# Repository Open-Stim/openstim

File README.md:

# <P align="center"> OPEN-STIM - OPEN SOURCE HARDWARE ARDUINO BASED ELECTRICAL STIMULATOR 
<table align='center'>
<tr align='center'>
<td align='center'>

Licence | OSHWA |
:-------------------------:|:-------------------------:|
 |  

</table> 
 
## <P align="center"> FEDERAL UNIVERSITY OF SÃO JOÃO DEL-REI – UFSJ
### <P align="center"> NEUROENGINEERING AND NEUROSCIENCE INTERDISCIPLINARY LABORATORY – LINNCE
&emsp; &emsp; &emsp; &emsp; &emsp; &emsp; &emsp; &emsp; &emsp; &emsp; &emsp; &emsp; &emsp; &emsp; &emsp; &emsp; &emsp; 

### DEVELOPED BY:
Maikon Lorran Santos - maikon.lorran@hotmail.com <br/>
João Daniel Nolasco - joaodani@hotmail.com <br/>
Vinícius Rosa Cota: - vrcota@ufsj.edu.br <br/>

### PROJECT'S GOAL
<P align="justify"> The main objective of the project was to develop and build a low-cost electrical stimulator for experimental stimulation electrophysiology
based on the Arduino platform, maximizing ease of use, versatility, and openness. The idea was to develop an output stage shield capable of 
delivering mono or biphasic pulses with constant current (even in face of varying output impedances) easily attachable to an Arduino microcontroller
board. Stimulation parameters (pulse frequency, pulse duration, number and polarity of phases) can be controlled by a touch screen and/or by knobs.
In this entry, we published the version which is controlled mostly by a touch screen display, but this can be easily substituted by manual controls 
(switches and additional knobs) with or without a LCD display to further reduce costs (variation not yet published). These variations and openness of 
the design (which is provisionally certified by OSHWA with UID BR000007) makes Open Stim a very flexible stimulation platform for experienced users and, 
at the same time, also a ready-to-use device for researchers not skilled on electronics. 

### DISCLAIMER
<P align="justify"> We offer this design as is and although it has been successfully tested with care and to the best of our knowledge, we do not provide any 
 warranty in any aspect.

### STIMULATOR PARAMETERS
-Current: 15 µA up to 1200 µA <br/>
-Frequency: 0.1 Hz up to 300 Hz <br/>
-Duty Cycle: 4 µs up to 1 s <br/>
-Biphasic Pulses <br/>
-Low battery indicator <br/>

### OPEN STIM

&emsp; &emsp; &emsp; 
### • More about the lab, at our website: [LINNce](https://ufsj.edu.br/vrcota/linnce.php)

### LICENSE
##### Documentation licensed under the Creative Commons Attribution Share Alike 4.0 International License

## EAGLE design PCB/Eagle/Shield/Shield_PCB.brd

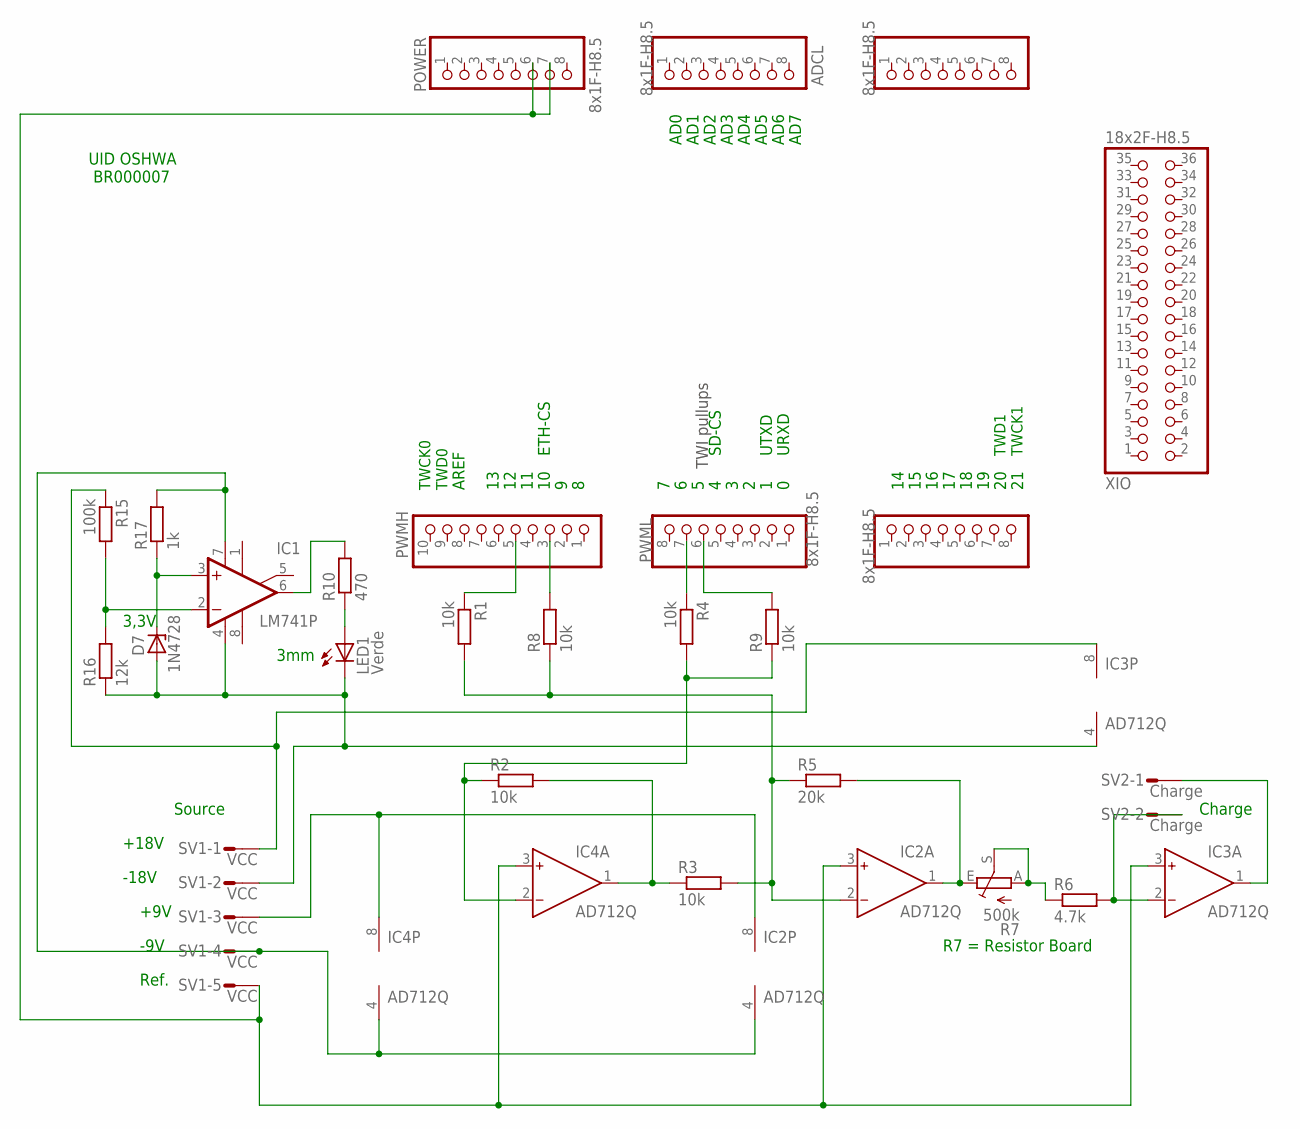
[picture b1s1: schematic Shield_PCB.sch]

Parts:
ADCH: 8x1F-H8.5; 1X08
ADCL: 8x1F-H8.5; 1X08
COMMUNICATION: 8x1F-H8.5; 1X08
D7: 1N4728; DO41Z10
IC1: LM741P; DIL08
IC2, IC3, IC4: AD712Q; DIL08
LED1: Verde; LED3MM
POWER: 8x1F-H8.5; 1X08
PWMH: 10x1F-H8.5; 1X10
PWML: 8x1F-H8.5; 1X08
R1, R2, R3, R4, R8, R9: 10k; 0207/10
R5: 20k; 0207/10
R6: 4.7k; 0207/10
R7: 500k; B64Y
R10: 470; 0207/10
R15: 100k; 0207/10
R16: 12k; 0207/10
R17: 1k; 0207/10
SV1: VCC; L05P
SV2: Charge; L02P
XIO: 18x2F-H8.5; 2X18

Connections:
unnamed: IC4.2 (IN-), R2.1, R4.2, R9.1
unnamed: IC4.1 (OUT), R2.2, R3.1
unnamed: IC2.2 (IN-), R1.2, R3.2, R5.1, R8.1
unnamed: IC2.1 (OUT), R5.2, R7.E
unnamed: IC3.2 (IN-), R6.2, SV2.2
unnamed: R6.1, R7.A, R7.S
unnamed: IC3.1 (OUT), SV2.1
unnamed: PWMH.3, R8.2
unnamed: PWMH.5, R1.1
unnamed: PWML.7, R4.1
unnamed: PWML.6, R9.2
unnamed: IC3.8 (V+), R15.1, SV1.1
unnamed: D7.A, IC1.4 (V-), IC3.4 (V-), LED1.K (C), R16.1, SV1.2
unnamed: IC1.7 (V+), IC2.4 (V-), IC4.4 (V-), R17.2, SV1.4
unnamed: IC2.3 (IN+), IC3.3 (IN+), IC4.3 (IN+), POWER.6, POWER.7, SV1.5
unnamed: D7.C, IC1.3 (+IN), R17.1
unnamed: IC1.2 (-IN), R15.2, R16.2
unnamed: IC1.6 (OUT), R10.2
unnamed: LED1.A, R10.1
unnamed: IC2.8 (V+), IC4.8 (V+), SV1.3

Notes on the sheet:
TWI pullups
TWCK1
TWD1
TWCK0
TWD0
AD1
AD2
AD3
AD4
AD5
AD6
AD0
AREF
AD7
SD-CS
UTXD
URXD
ETH-CS
Source
Charge
R7 = Resistor Board
3,3V
3mm
+18V
-18V
+9V
-9V
Ref.
UID OSHWA BR000007

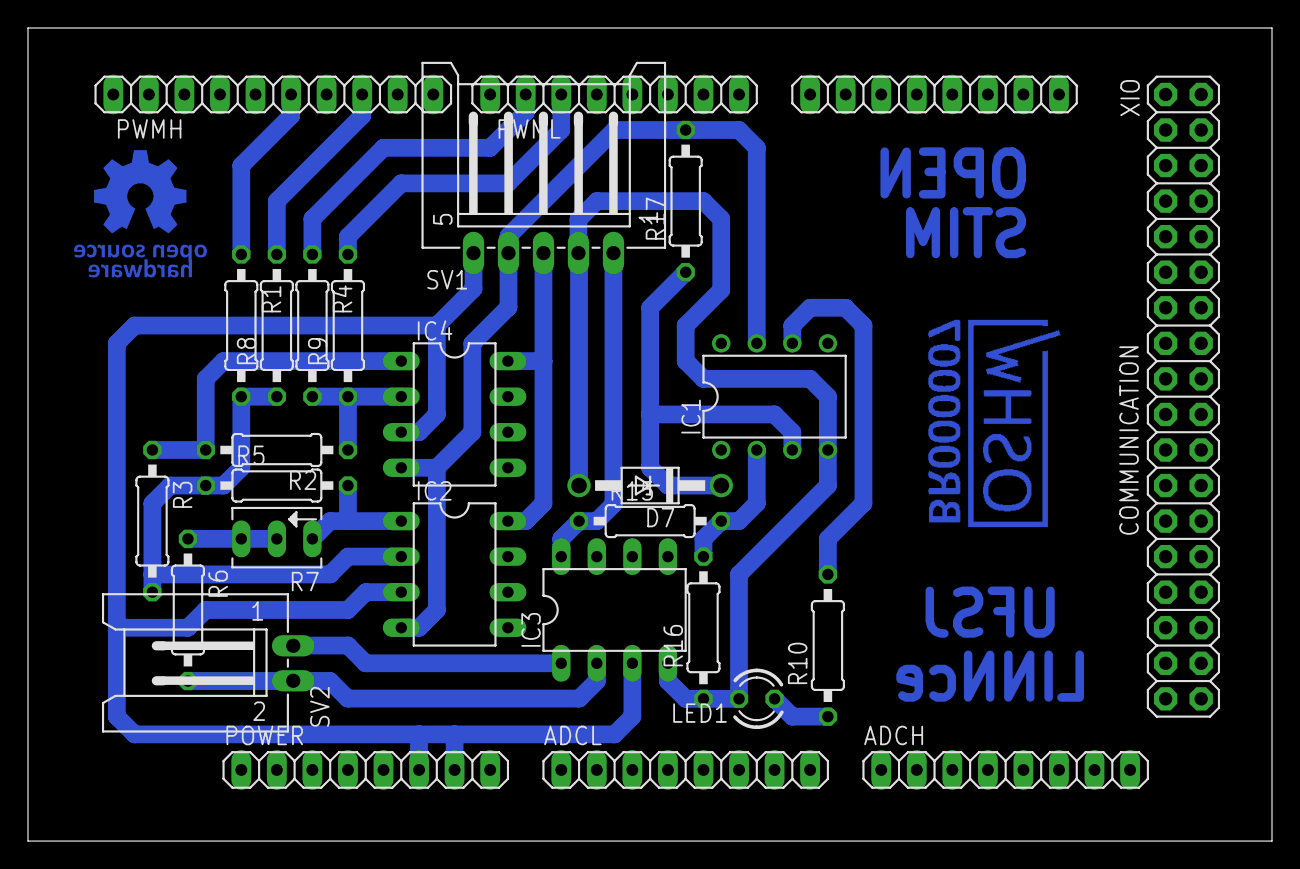
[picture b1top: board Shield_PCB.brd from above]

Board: 2 copper layers, 88.9 x 58.1 mm, 28 parts (0 on the bottom side), 20 nets.

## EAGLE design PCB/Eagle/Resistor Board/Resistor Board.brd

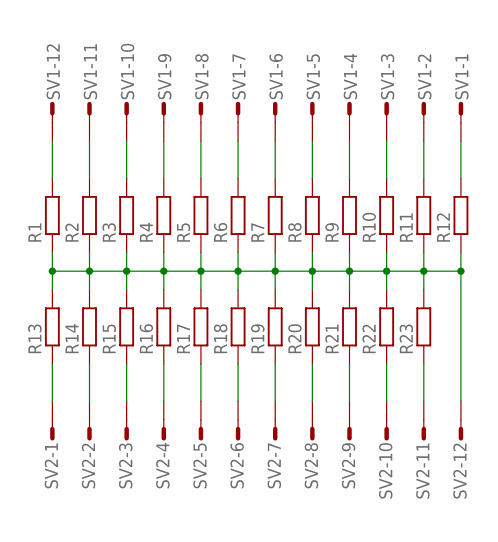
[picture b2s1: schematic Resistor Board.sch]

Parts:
R1, R2, R3, R4, R5, R6, R7, R8, R9, R10, R11, R12, R13, R14, R15, R16, R17, R18, R19, R20, R21, R22, R23: R-EU_0207/10; 0207/10
SV1, SV2: S12P

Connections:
unnamed: R13.1, SV2.1
unnamed: R14.1, SV2.2
unnamed: R15.1, SV2.3
unnamed: R16.1, SV2.4
unnamed: R17.1, SV2.5
unnamed: R18.1, SV2.6
unnamed: R19.1, SV2.7
unnamed: R20.1, SV2.8
unnamed: R21.1, SV2.9
unnamed: R22.1, SV2.10
unnamed: R23.1, SV2.11
unnamed: R1.2, SV1.12
unnamed: R1.1, R2.1, R3.1, R4.1, R5.1, R6.1, R7.1, R8.1, R9.1, R10.1, R11.1, R12.1, R13.2, R14.2, R15.2, R16.2, R17.2, R18.2, R19.2, R20.2, R21.2, R22.2, R23.2, SV2.12
unnamed: R2.2, SV1.11
unnamed: R3.2, SV1.10
unnamed: R4.2, SV1.9
unnamed: R5.2, SV1.8
unnamed: R6.2, SV1.7
unnamed: R7.2, SV1.6
unnamed: R8.2, SV1.5
unnamed: R9.2, SV1.4
unnamed: R10.2, SV1.3
unnamed: R11.2, SV1.2
unnamed: R12.2, SV1.1

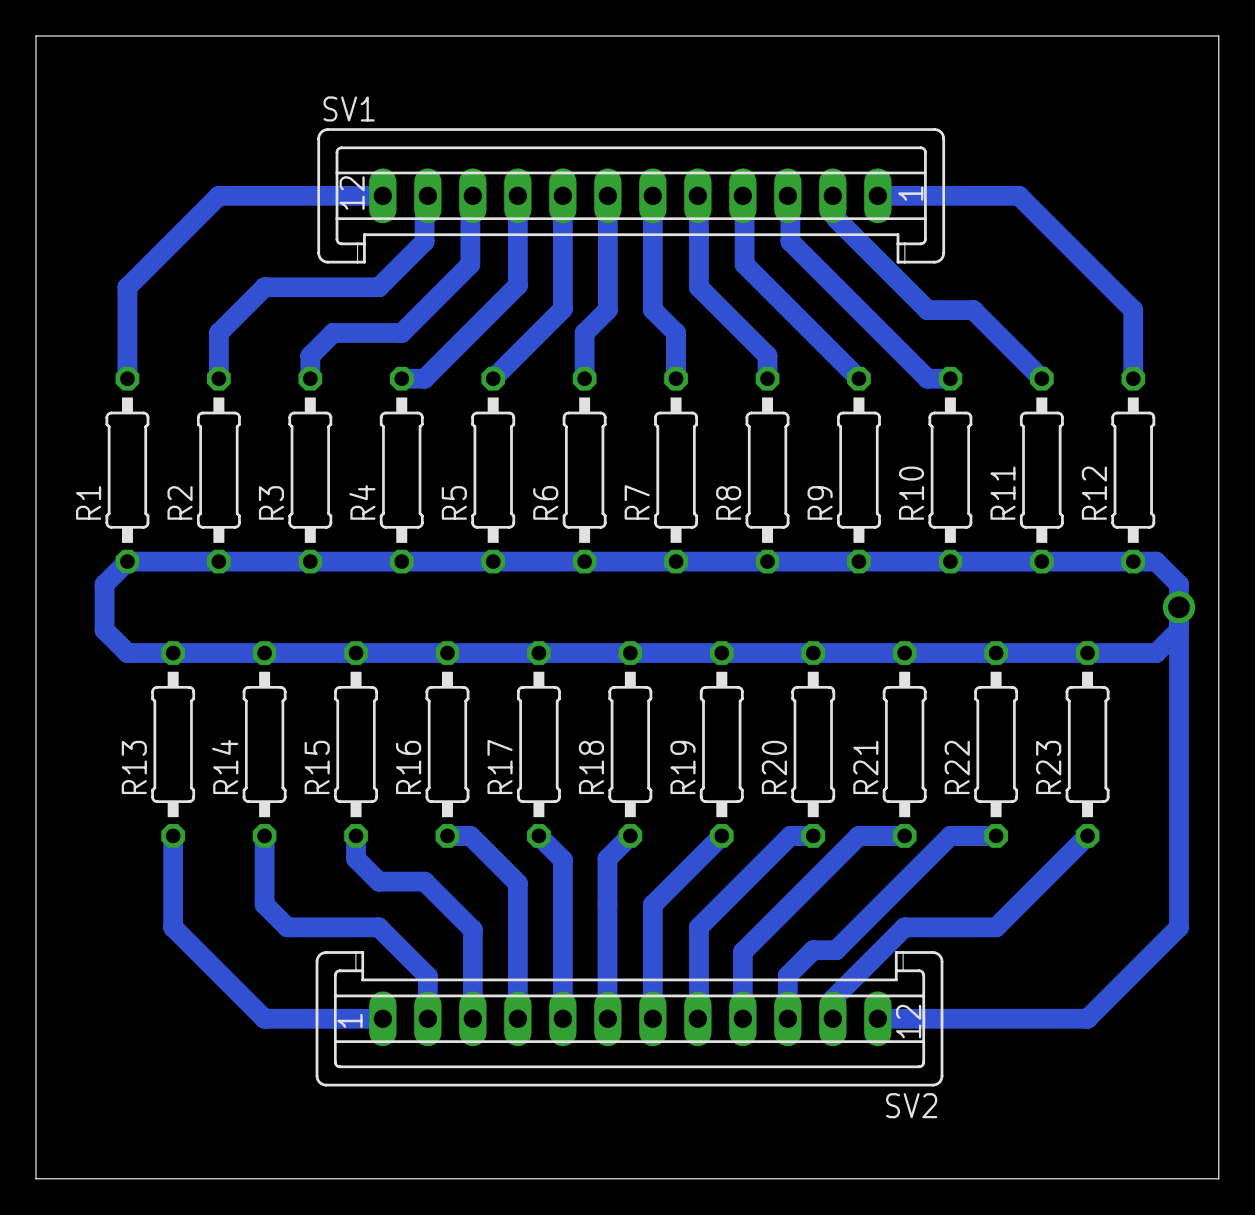
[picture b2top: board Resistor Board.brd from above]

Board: 2 copper layers, 65.7 x 63.5 mm, 25 parts (0 on the bottom side), 24 nets.

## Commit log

2021-04-12 Creative Commons Attribution 4.0 International
2021-04-13 Delete Alpargatas.docx
    excluir
2021-04-13 exclusão bbb
2021-06-30 3D Printing
2021-06-30 Arduino Code
2021-06-30 B.O.M
2021-06-30 Licenses
2021-06-30 Manual
2021-06-30 Nextion Code
2021-06-30 Photos
2021-06-30 Simulation and Diagram
2021-06-30 Test
2021-06-30 Libraries
2021-06-30 Arduino Library
2021-06-30 Additional Files
2021-07-01 Open-Stim
2021-07-01 Shield
2021-07-01 Open Source Hardware UID OSHWA
2021-07-01 LINNce
2021-07-01 UFSJ
2021-08-10 Licenses_OSHWA
2021-09-02 Incluindo código para o ESP8266
2021-10-07 Licence hardware
2021-10-07 Licence - Hardware
2021-10-07 Licence
2021-10-07 Licences
